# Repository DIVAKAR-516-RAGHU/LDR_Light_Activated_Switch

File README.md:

# LDR Light-Activated Switch Using KiCad

## Project Overview

This project presents the schematic design and PCB layout of a **6 V DC LDR Light-Activated Switch** developed using KiCad. The circuit uses a Light Dependent Resistor (LDR) to detect ambient light and an NPN BC547 transistor to control an LED automatically.

The project covers circuit schematic design, component footprint assignment, PCB layout, Design Rule Checking (DRC), and Gerber and drill file generation.

## Objectives

- Design a light-sensitive switching circuit.
- Understand LDR-based voltage dividers.
- Use an NPN transistor as an electronic switch.
- Design a PCB using KiCad.
- Generate manufacturing files for PCB fabrication.

## Components Used

| Component | Value / Description | Quantity |
|---|---|---:|
| J1 | 2-pin, 6 V DC input connector | 1 |
| R1 | 10 kΩ resistor | 1 |
| R2 | 470 Ω resistor | 1 |
| R3 | Light Dependent Resistor (LDR) | 1 |
| R4 | 10 kΩ resistor | 1 |
| Q1 | BC547 NPN transistor | 1 |
| D1 | LED | 1 |

## Tools Used

- **KiCad** — Schematic capture and PCB design
- **PCB Editor** — Component placement and copper routing
- **DRC** — PCB design rule verification
- **Gerber Viewer** — Manufacturing file inspection

## Working Principle

The LDR changes its resistance according to the intensity of the light falling on it. Together with R1, it forms a voltage divider that produces a light-dependent voltage at the `LIGHT_SENSE` node.

The BC547 transistor receives this signal through R4 and operates as a switch. The LED is connected to the 6 V supply through a 470 Ω current-limiting resistor.

- **Bright light:** The LDR resistance decreases, raising the voltage at `LIGHT_SENSE`. The transistor turns on, and the LED lights up.
- **Low light or darkness:** The LDR resistance increases, lowering the voltage at `LIGHT_SENSE`. The transistor turns off, and the LED goes off.

*Note: The actual switching threshold depends on the LDR characteristics and the selected resistor values. The circuit should be tested to confirm its behavior.*

## Design Workflow

1. Created the circuit schematic in KiCad.
2. Connected the power supply, LDR voltage divider, transistor switch, and LED output.
3. Assigned component footprints.
4. Transferred the schematic to PCB Editor.
5. Arranged the components and routed the copper tracks.
6. Ran the Design Rule Checker (DRC).
7. Generated Gerber and drill files for manufacturing.

## PCB Design Verification

- Schematic Electrical Rules Check (ERC) completed.
- PCB Design Rule Check (DRC) reported zero errors.
- Gerber and drill files generated.

Zero DRC errors do not independently guarantee electrical correctness. Component pin mapping, connector polarity, LED orientation, and manufacturing files must also be verified before fabrication.

## Applications

- Automatic light-sensitive indicators
- Basic light-detection circuits
- Electronics learning and prototyping
- Introductory PCB design practice

## Future Improvements

- Add an adjustable light-sensitivity threshold.
- Replace the fixed switching threshold with a comparator circuit.
- Add a relay or MOSFET output stage for suitable external loads.
- Assemble and test the fabricated PCB under different lighting conditions.

## Learning Outcomes

This project provided practical experience with analog sensor interfacing, voltage-divider circuits, transistor switching, schematic capture, footprint assignment, PCB routing, DRC, and manufacturing file generation.

## Author

**Divakar R**  
B.E. Electronics and Communication Engineering  
Adithya Institute of Technology, Coimbatore, Tamil Nadu, India

## License

This project is intended for educational and prototyping purposes. A formal license can be added if the design is distributed or reused publicly.

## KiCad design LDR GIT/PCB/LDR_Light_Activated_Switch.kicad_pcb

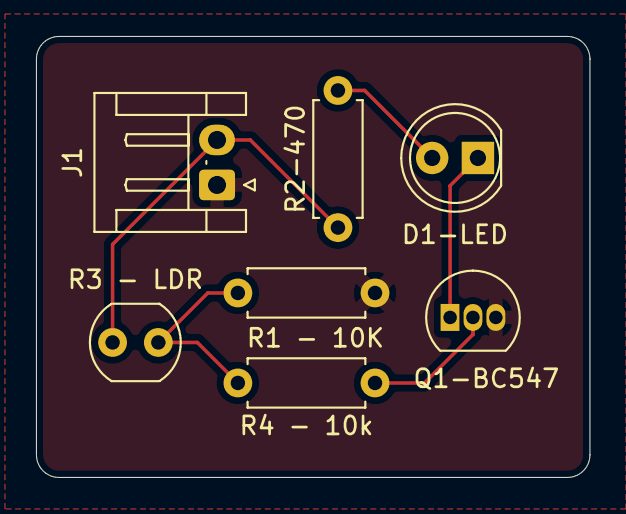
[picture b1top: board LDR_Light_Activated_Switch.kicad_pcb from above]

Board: 2 copper layers, 30.8 x 24.5 mm, 7 parts (0 on the bottom side), 6 nets.

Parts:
D1-LED: LED; LED_D5.0mm
J1: Conn_01x02; JST_EH_S2B-EH_1x02_P2.50mm_Horizontal
Q1-BC547: BC547; TO-92_Inline
R1 - 10K, R4 - 10k: 10k; R_Axial_DIN0207_L6.3mm_D2.5mm_P7.62mm_Horizontal
R2-470: 470; R_Axial_DIN0207_L6.3mm_D2.5mm_P7.62mm_Horizontal
R3 - LDR: R_Photo; R_LDR_4.9x4.2mm_P2.54mm_Vertical

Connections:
+6V: J1.2, R2-470.1, R3 - LDR.1
/B: Q1-BC547.2 (B), R4 - 10k.1
/LIGHT_SENSE: R1 - 10K.1, R3 - LDR.2, R4 - 10k.2
GND: J1.1, Q1-BC547.3 (E), R1 - 10K.2
unnamed: D1-LED.2 (A), R2-470.2
unnamed: D1-LED.1 (K), Q1-BC547.1 (C)
